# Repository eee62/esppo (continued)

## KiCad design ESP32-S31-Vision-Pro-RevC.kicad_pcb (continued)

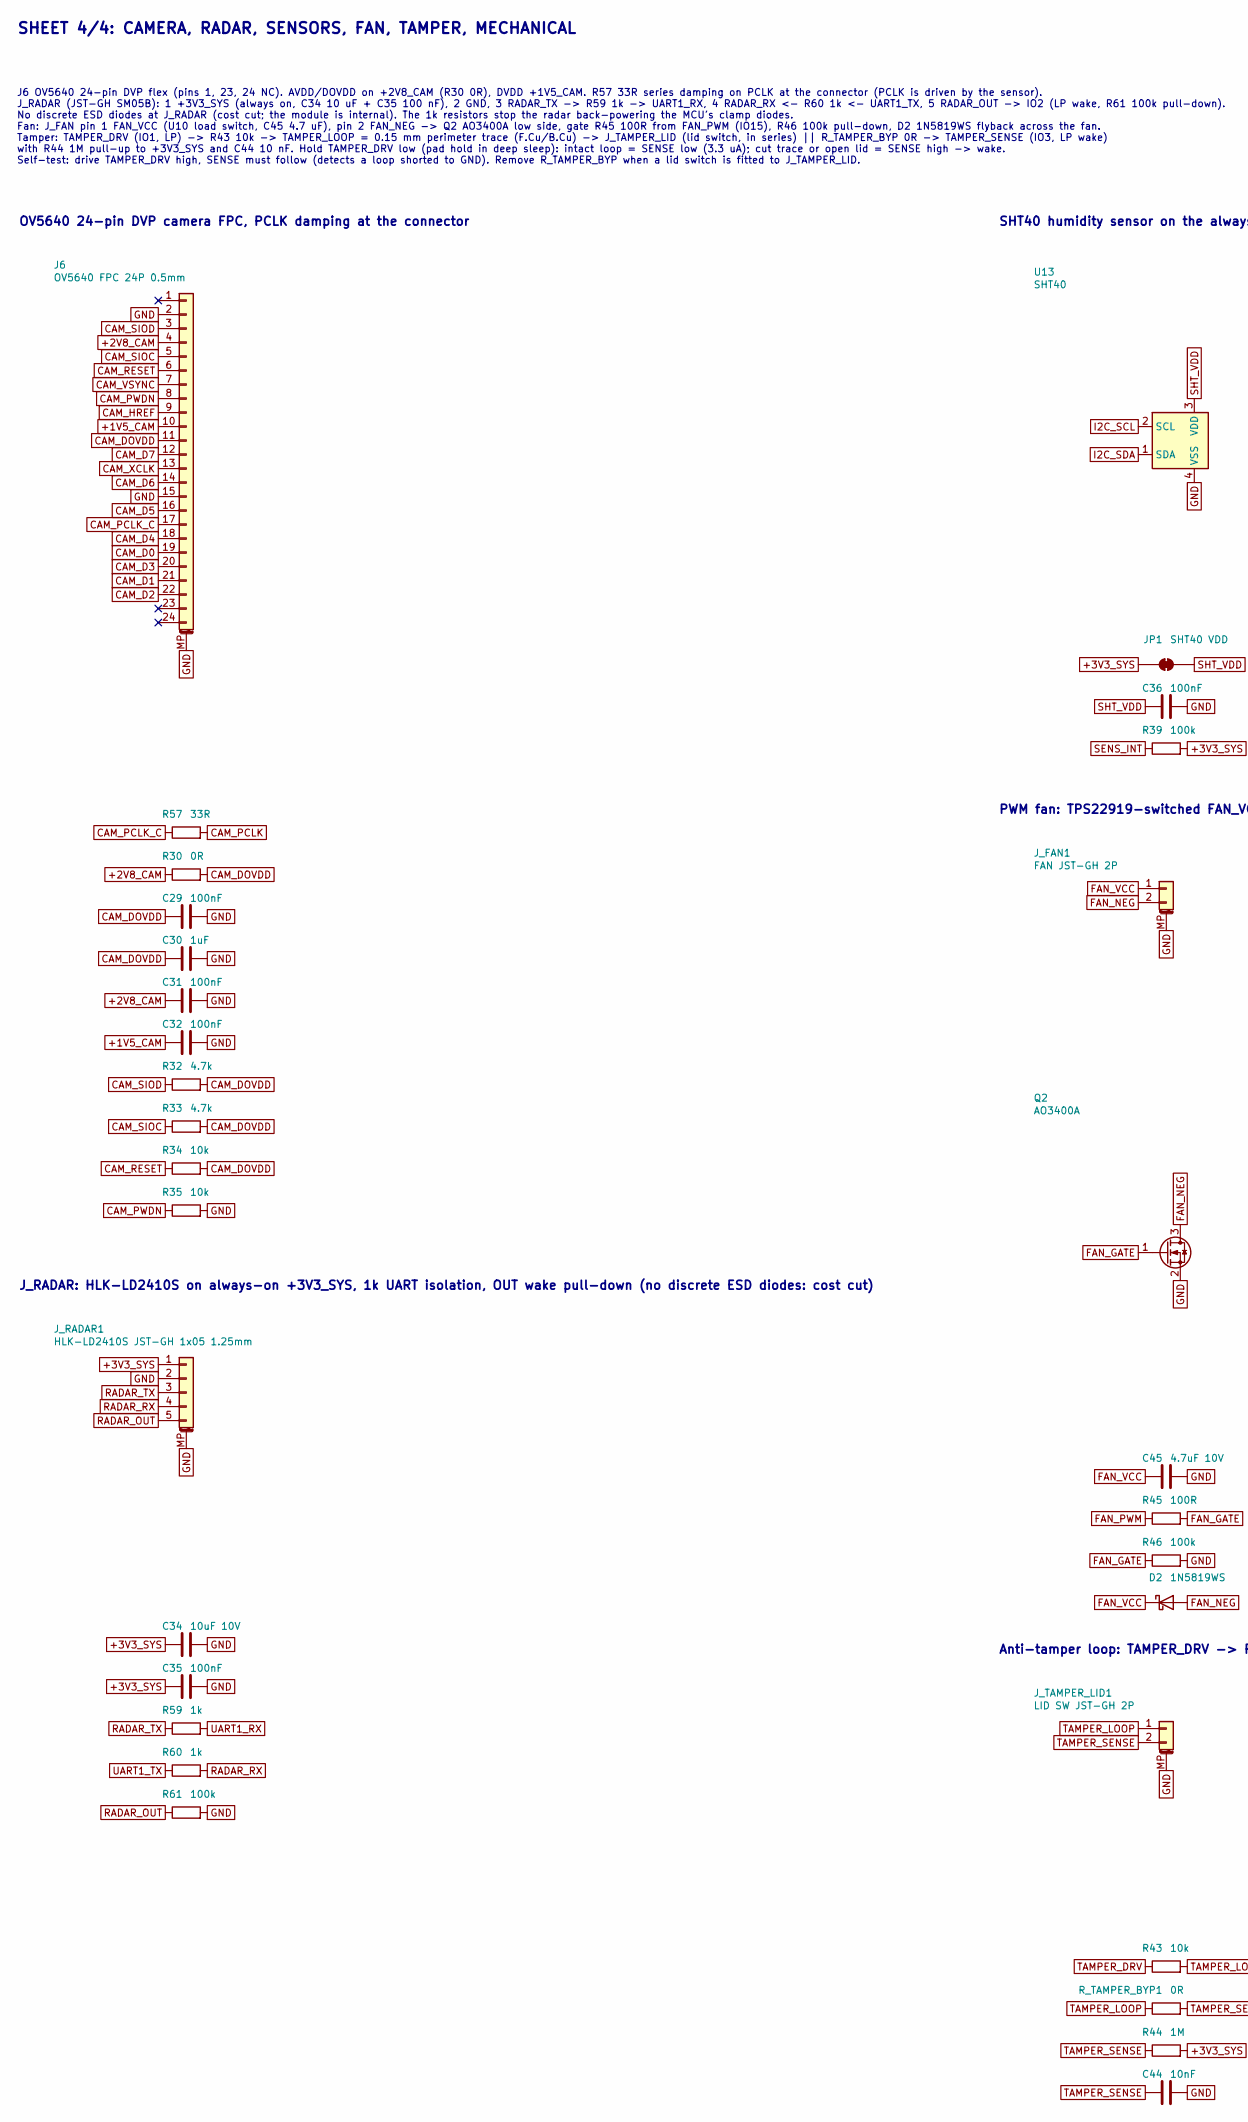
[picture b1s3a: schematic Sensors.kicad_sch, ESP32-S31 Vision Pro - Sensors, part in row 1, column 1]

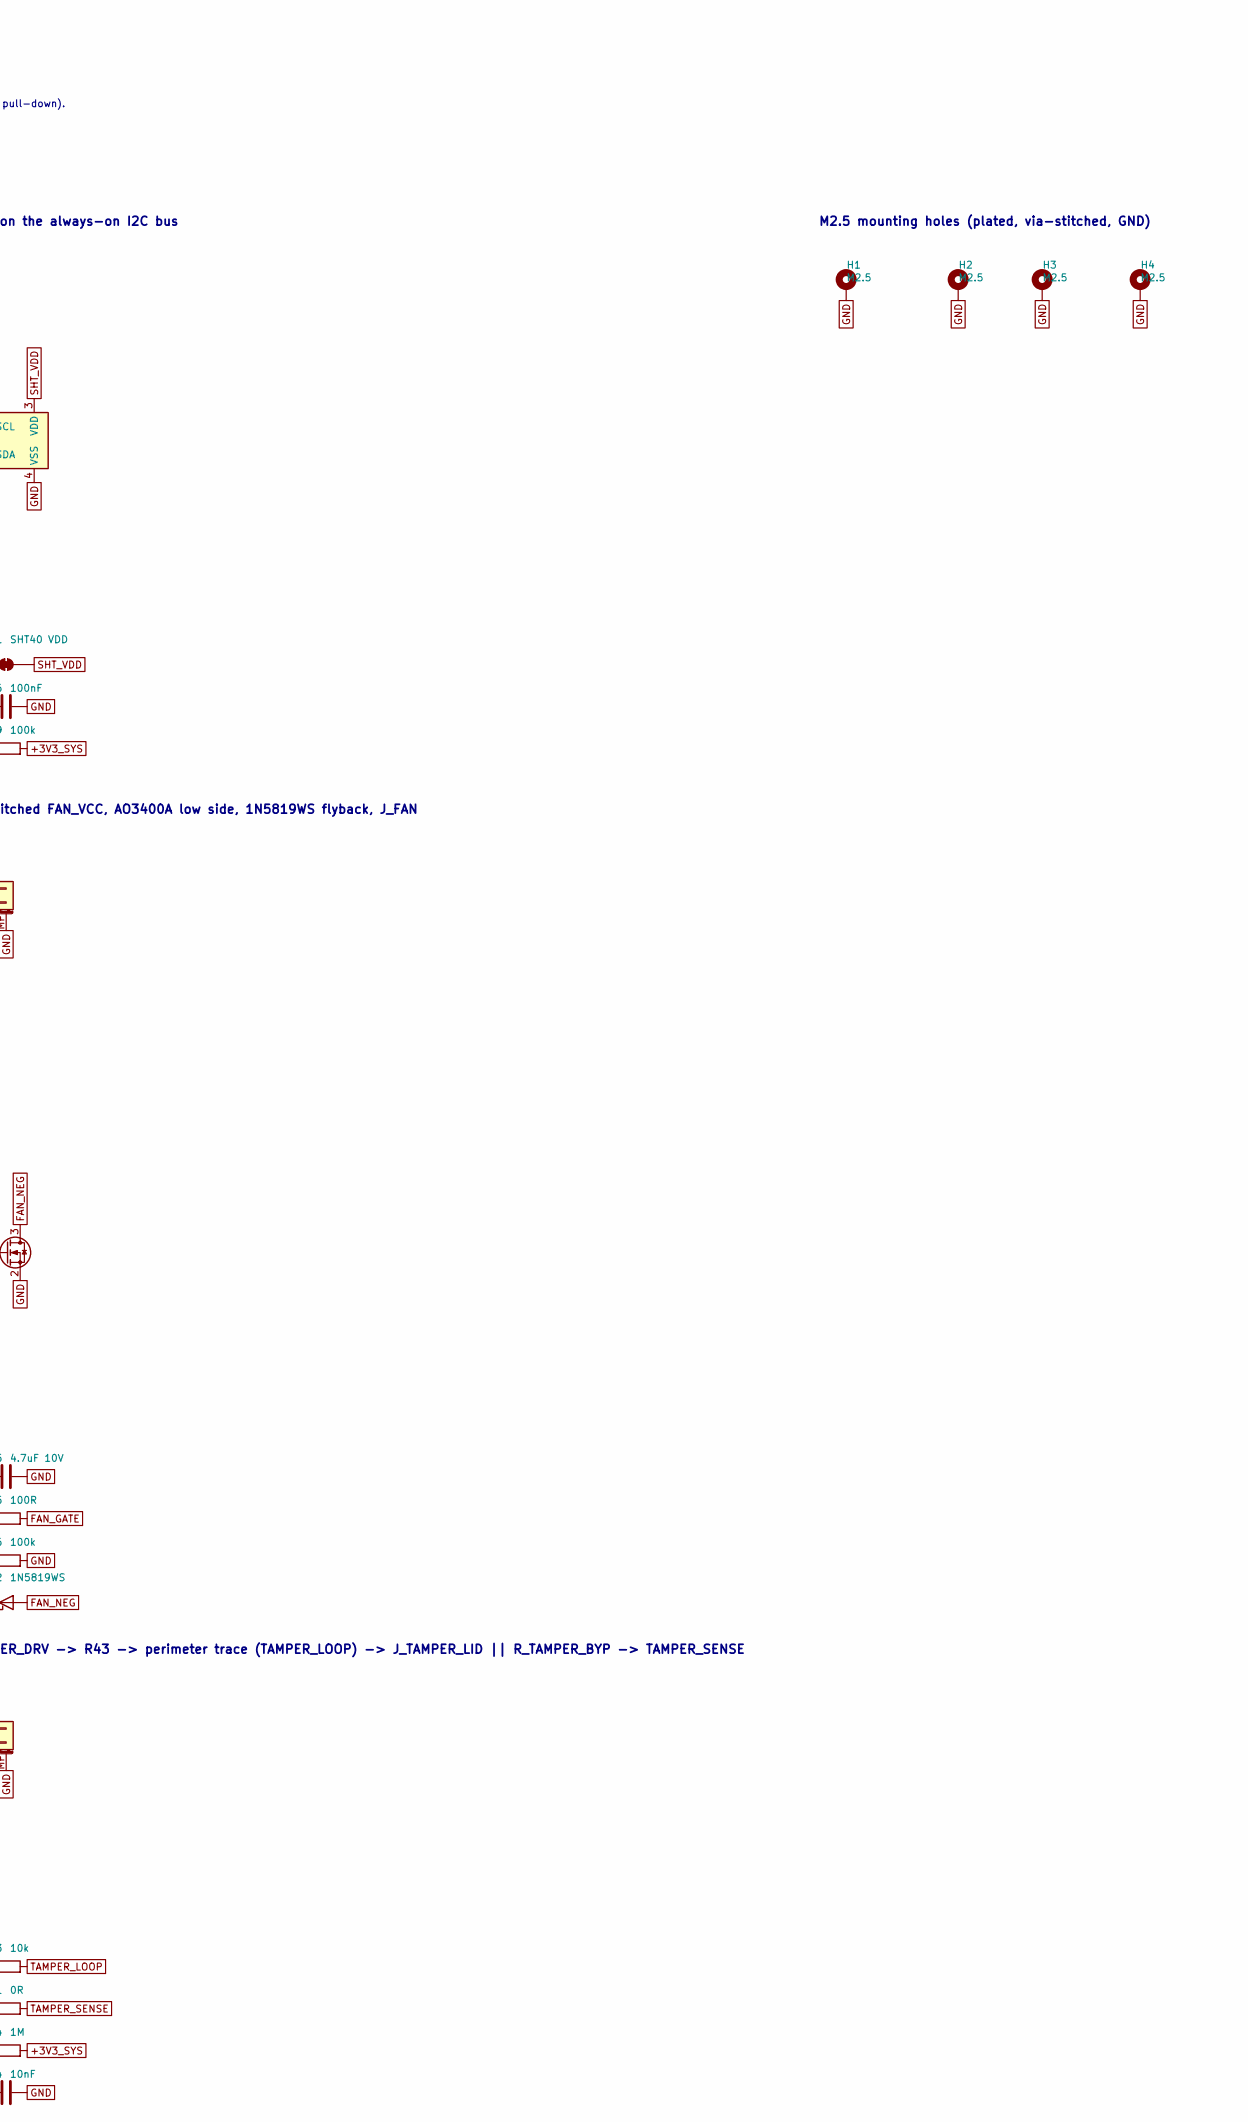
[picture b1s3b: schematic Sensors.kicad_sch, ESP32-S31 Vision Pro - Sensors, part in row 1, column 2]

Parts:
C29, C31, C32, C35, C36: 100nF; C_0402_1005Metric; MPN CL05B104KO5NNNC; LCSC C1525
C30: 1uF; C_0402_1005Metric; MPN CL05A105KA5NQNC; LCSC C52923
C34: 10uF 10V; C_0603_1608Metric; MPN CL10A106KP8NNNC; LCSC C19702
C44: 10nF; C_0402_1005Metric; MPN CL05B103KB5NNNC; LCSC C15195
C45: 4.7uF 10V; C_0603_1608Metric; MPN CL10A475KO8NNNC; LCSC C19666
D2: 1N5819WS; D_SOD-323; MPN 1N5819WS; LCSC C191023
H1, H2, H3, H4: M2.5; MountingHole_2.7mm_M2.5_Pad_Via
J6: OV5640 FPC 24P 0.5mm; Hirose_FH12-24S-0.5SH_1x24-1MP_P0.50mm_Horizontal; MPN FH12-24S-0.5SH(55); LCSC C202112
JP1: SHT40 VDD; SolderJumper-2_P1.3mm_Bridged_RoundedPad1.0x1.5mm
J_FAN1: FAN JST-GH 2P; JST_GH_SM02B-GHS-TB_1x02-1MP_P1.25mm_Horizontal; MPN A1257WR-S-2P; LCSC C225125
J_RADAR1: HLK-LD2410S JST-GH 1x05 1.25mm; JST_GH_SM05B-GHS-TB_1x05-1MP_P1.25mm_Horizontal; MPN SM05B-GHS-TB(LF)(SN); LCSC C189896
J_TAMPER_LID1: LID SW JST-GH 2P; JST_GH_SM02B-GHS-TB_1x02-1MP_P1.25mm_Horizontal; MPN A1257WR-S-2P; LCSC C225125
Q2: AO3400A; SOT-23; MPN AO3400A; LCSC C20917
R30: 0R; R_0402_1005Metric; MPN 0402WGF0000TCE; LCSC C17168
R32, R33: 4.7k; R_0402_1005Metric; MPN 0402WGF4701TCE; LCSC C25900
R34, R35, R43: 10k; R_0402_1005Metric; MPN 0402WGF1002TCE; LCSC C25744
R39, R46, R61: 100k; R_0402_1005Metric; MPN 0402WGF1003TCE; LCSC C25741
R44: 1M; R_0402_1005Metric; MPN 0402WGF1004TCE; LCSC C26083
R45: 100R; R_0402_1005Metric; MPN 0402WGF1000TCE; LCSC C25076
R57: 33R; R_0402_1005Metric; MPN 0402WGF330JTCE; LCSC C25105
R59, R60: 1k; R_0402_1005Metric; MPN 0402WGF1001TCE; LCSC C11702
R_TAMPER_BYP1: 0R; R_0603_1608Metric; MPN 0603WAF0000T5E; LCSC C21189
U13: SHT40; Sensirion_DFN-4_1.5x1.5mm_P0.8mm_SHT4x_NoCentralPad; MPN SHT40-AD1F-R2; LCSC C7461846

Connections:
+1V5_CAM: C32.1, J6.10; also elsewhere on the board
+2V8_CAM: C31.1, J6.4, R30.1; also elsewhere on the board
+3V3_SYS: C34.1, C35.1, JP1.1 (A), J_RADAR1.1, R39.2, R44.2; also elsewhere on the board
CAM_D0: J6.19; also elsewhere on the board
CAM_D1: J6.21; also elsewhere on the board
CAM_D2: J6.22; also elsewhere on the board
CAM_D3: J6.20; also elsewhere on the board
CAM_D4: J6.18; also elsewhere on the board
CAM_D5: J6.16; also elsewhere on the board
CAM_D6: J6.14; also elsewhere on the board
CAM_D7: J6.12; also elsewhere on the board
CAM_DOVDD: C29.1, C30.1, J6.11, R30.2, R32.2, R33.2, R34.2
CAM_HREF: J6.9; also elsewhere on the board
CAM_PCLK: R57.2; also elsewhere on the board
CAM_PCLK_C: J6.17, R57.1
CAM_PWDN: J6.8, R35.1; also elsewhere on the board
CAM_RESET: J6.6, R34.1; also elsewhere on the board
CAM_SIOC: J6.5, R33.1; also elsewhere on the board
CAM_SIOD: J6.3, R32.1; also elsewhere on the board
CAM_VSYNC: J6.7; also elsewhere on the board
CAM_XCLK: J6.13; also elsewhere on the board
FAN_GATE: Q2.1 (G), R45.2, R46.1
FAN_NEG: D2.2 (A), J_FAN1.2, Q2.3 (D)
FAN_PWM: R45.1; also elsewhere on the board
FAN_VCC: C45.1, D2.1 (K), J_FAN1.1; also elsewhere on the board
GND: C29.2, C30.2, C31.2, C32.2, C34.2, C35.2, C36.2, C44.2, C45.2, H1.1, H2.1, H3.1, H4.1, J6.2, J6.15, J6.MP (MountPin), J_FAN1.MP (MountPin), J_RADAR1.2, J_RADAR1.MP (MountPin), J_TAMPER_LID1.MP (MountPin), Q2.2 (S), R35.2, R46.2, R61.2, U13.4 (VSS); also elsewhere on the board
I2C_SCL: U13.2 (SCL); also elsewhere on the board
I2C_SDA: U13.1 (SDA); also elsewhere on the board
RADAR_OUT: J_RADAR1.5, R61.1; also elsewhere on the board
RADAR_RX: J_RADAR1.4, R60.2
RADAR_TX: J_RADAR1.3, R59.1
SENS_INT: R39.1; also elsewhere on the board
SHT_VDD: C36.1, JP1.2 (B), U13.3 (VDD)
TAMPER_DRV: R43.1; also elsewhere on the board
TAMPER_LOOP: J_TAMPER_LID1.1, R43.2, R_TAMPER_BYP1.1
TAMPER_SENSE: C44.1, J_TAMPER_LID1.2, R44.1, R_TAMPER_BYP1.2; also elsewhere on the board
UART1_RX: R59.2; also elsewhere on the board
UART1_TX: R60.1; also elsewhere on the board

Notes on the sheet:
SHEET 4/4: CAMERA, RADAR, SENSORS, FAN, TAMPER, MECHANICAL
J6 OV5640 24-pin DVP flex (pins 1, 23, 24 NC). AVDD/DOVDD on +2V8_CAM (R30 0R), DVDD +1V5_CAM. R57 33R series damping on PCLK at the connector (PCLK is driven by the sensor). J_RADAR (JST-GH SM05B): 1 +3V3_SYS (always on, C34 10 uF + C35 100 nF), 2 GND, 3 RADAR_TX -> R59 1k -> UART1_RX, 4 RADAR_RX 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
OV5640 24-pin DVP camera FPC, PCLK damping at the connector
J_RADAR: HLK-LD2410S on always-on +3V3_SYS, 1k UART isolation, OUT wake pull-down (no discrete ESD diodes: cost cut)
SHT40 humidity sensor on the always-on I2C bus
PWM fan: TPS22919-switched FAN_VCC, AO3400A low side, 1N5819WS flyback, J_FAN
Anti-tamper loop: TAMPER_DRV -> R43 -> perimeter trace (TAMPER_LOOP) -> J_TAMPER_LID || R_TAMPER_BYP -> TAMPER_SENSE
M2.5 mounting holes (plated, via-stitched, GND)

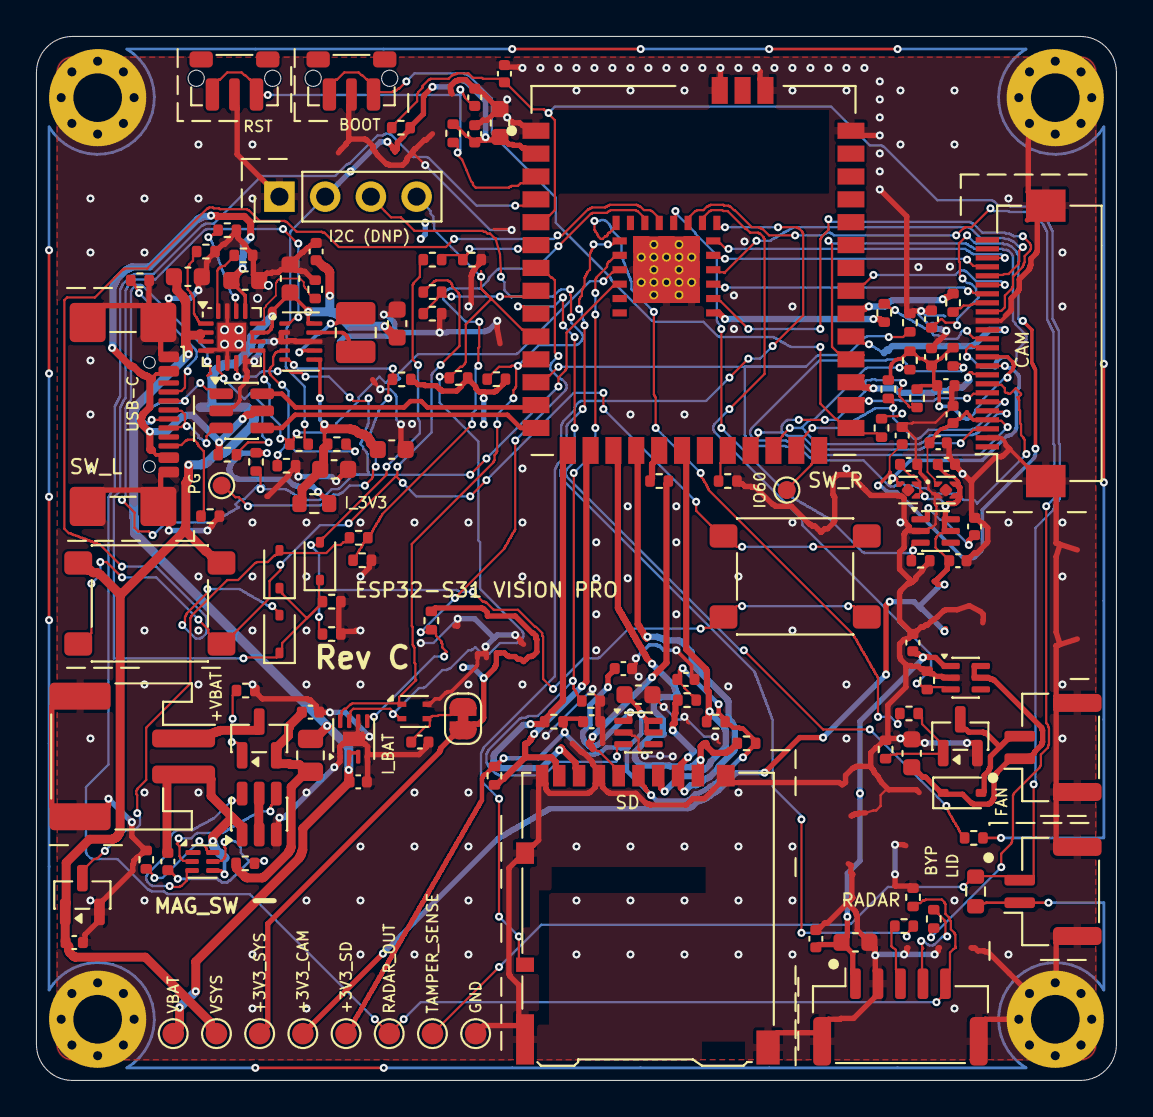
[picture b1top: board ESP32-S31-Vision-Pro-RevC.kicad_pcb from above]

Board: 4 copper layers, 60.0 x 58.0 mm, 137 parts (0 on the bottom side), 94 nets.

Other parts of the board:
C18: 22uF 6.3V; C_0603_1608Metric
C19: 100nF; C_0402_1005Metric
C20: 1uF; C_0402_1005Metric
J3: I2C 1x04 2.54mm header (DNP); PinHeader_1x04_P2.54mm_Vertical
R12, R13, R14: 10k; R_0402_1005Metric
R19, R20: 4.7k; R_0402_1005Metric
R22: 33R; R_0402_1005Metric
SW_BOOT1: BOOT (IO61); SW_Push_1P1T-MP_NO_Horizontal_Alps_SKRTLAE010
SW_RST1: RESET (EN); SW_Push_1P1T-MP_NO_Horizontal_Alps_SKRTLAE010
TP2: IO60; TestPoint_Pad_D1.0mm
U8: ESP32-S31-WROOM-1U

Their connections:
+3V3_SYS: C18.1, C19.1, J3.2, R12.2, R13.2, R19.2, R20.2, U8.2; also elsewhere on the board
CAM_D0: U8.33; also elsewhere on the board
CAM_D1: U8.60; also elsewhere on the board
CAM_D2: U8.61; also elsewhere on the board
CAM_D3: U8.59; also elsewhere on the board
CAM_D4: U8.58; also elsewhere on the board
CAM_D5: U8.57; also elsewhere on the board
CAM_D6: U8.31; also elsewhere on the board
CAM_D7: U8.30; also elsewhere on the board
CAM_HREF: U8.29; also elsewhere on the board
CAM_PCLK: U8.32; also elsewhere on the board
CAM_PWDN: U8.12; also elsewhere on the board
CAM_RESET: U8.25; also elsewhere on the board
CAM_SIOC: U8.24; also elsewhere on the board
CAM_SIOD: U8.23; also elsewhere on the board
CAM_VSYNC: U8.28; also elsewhere on the board
CAM_XCLK: R22.2; also elsewhere on the board
CAM_XCLK_R: R22.1, U8.56
CHG_PGOOD: U8.53; also elsewhere on the board
CHG_STAT: U8.52; also elsewhere on the board
EN_CAM: U8.45; also elsewhere on the board
EN_FAN: U8.43; also elsewhere on the board
EN_SD: U8.51; also elsewhere on the board
ESP_BOOT: R13.1, SW_BOOT1.1, U8.27
ESP_EN: C20.1, R12.1, SW_RST1.1, U8.3
ESP_IO60: TP2.1, U8.26
FAN_PWM: U8.49; also elsewhere on the board
GND: C18.2, C19.2, C20.2, J3.1, R14.2, SW_BOOT1.2, SW_RST1.2, U8.1, U8.40, U8.41, U8.62, U8.64; also elsewhere on the board
HOLD: U8.46; also elsewhere on the board
I2C_SCL: J3.4, R20.1, U8.10; also elsewhere on the board
I2C_SDA: J3.3, R19.1, U8.11; also elsewhere on the board
JTAG_SEL: R14.1, U8.22
RADAR_OUT: U8.4; also elsewhere on the board
SD_CD: U8.42; also elsewhere on the board
SD_CLK_R: U8.19; also elsewhere on the board
SD_CMD: U8.20; also elsewhere on the board
SD_D0: U8.15; also elsewhere on the board
SD_D1: U8.16; also elsewhere on the board
SD_D2: U8.17; also elsewhere on the board
SD_D3: U8.18; also elsewhere on the board
SENSE_L: U8.8; also elsewhere on the board
SENSE_R: U8.6; also elsewhere on the board
SENS_INT: U8.7; also elsewhere on the board
TAMPER_DRV: U8.9; also elsewhere on the board
TAMPER_SENSE: U8.5; also elsewhere on the board
TMR_SENSE: U8.47; also elsewhere on the board
UART1_RX: U8.50; also elsewhere on the board
UART1_TX: U8.44; also elsewhere on the board
USB_DN: U8.13; also elsewhere on the board
USB_DP: U8.14; also elsewhere on the board

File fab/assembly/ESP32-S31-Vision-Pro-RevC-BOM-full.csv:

"Refs","Value","Footprint","Qty","MPN","LCSC","DNP"
"C1","2.2uF 16V","Capacitor_SMD:C_0603_1608Metric","1","CL10A225KO8NNNC","C23630",""
"C2,C45","4.7uF 10V","Capacitor_SMD:C_0603_1608Metric","2","CL10A475KO8NNNC","C19666",""
"C3,C4,C24,C34","10uF 10V","Capacitor_SMD:C_0603_1608Metric","4","CL10A106KP8NNNC","C19702",""
"C5,C19,C25,C29,C31,C32,C35,C36,C46,C47,C48,C49","100nF","Capacitor_SMD:C_0402_1005Metric","12","CL05B104KO5NNNC","C1525",""
"C6,C7,C18","22uF 6.3V","Capacitor_SMD:C_0603_1608Metric","3","CL10A226MQ8NRNC","C59461",""
"C10,C11,C12,C13,C14,C15,C16,C17,C20,C30,C52","1uF","Capacitor_SMD:C_0402_1005Metric","11","CL05A105KA5NQNC","C52923",""
"C44","10nF","Capacitor_SMD:C_0402_1005Metric","1","CL05B103KB5NNNC","C15195",""
"D2","1N5819WS","Diode_SMD:D_SOD-323","1","1N5819WS","C191023",""
"D_HOLD1,D_TMR1,D_WAKE1","BAT54WS","Diode_SMD:D_SOD-323","3","BAT54WS","C7502694",""
"H1,H2,H3,H4","M2.5","MountingHole:MountingHole_2.7mm_M2.5_Pad_Via","4","","",""
"J1","LiPo 1S <=3000mAh (JST-PH)","Connector_JST:JST_PH_S2B-PH-SM4-TB_1x02-1MP_P2.00mm_Horizontal","1","S2B-PH-SM4-TB(LF)(SN)","C295747",""
"J3","I2C 1x04 2.54mm header (DNP)","Connector_PinHeader_2.54mm:PinHeader_1x04_P2.54mm_Vertical","1","","","DNP"
"J5","USB-C","Connector_USB:USB_C_Receptacle_GCT_USB4110","1","USB4110-GF-A","C5143397",""
"J6","OV5640 FPC 24P 0.5mm","Connector_FFC-FPC:Hirose_FH12-24S-0.5SH_1x24-1MP_P0.50mm_Horizontal","1","FH12-24S-0.5SH(55)","C202112",""
"J9","microSD push-push DM3AT-SF-PEJM5","Connector_Card:microSD_HC_Hirose_DM3AT-SF-PEJM5","1","DM3AT-SF-PEJM5","C114218",""
"JP1","SHT40 VDD","Jumper:SolderJumper-2_P1.3mm_Bridged_RoundedPad1.0x1.5mm","1","","",""
"J_FAN1","FAN JST-GH 2P","Connector_JST:JST_GH_SM02B-GHS-TB_1x02-1MP_P1.25mm_Horizontal","1","A1257WR-S-2P","C225125",""
"J_RADAR1","HLK-LD2410S JST-GH 1x05 1.25mm","Connector_JST:JST_GH_SM05B-GHS-TB_1x05-1MP_P1.25mm_Horizontal","1","SM05B-GHS-TB(LF)(SN)","C189896",""
"J_TAMPER_LID1","LID SW JST-GH 2P","Connector_JST:JST_GH_SM02B-GHS-TB_1x02-1MP_P1.25mm_Horizontal","1","A1257WR-S-2P","C225125",""
"L1","0.47uH 4A","Inductor_SMD:L_1008_2520Metric","1","DFE252012F-R47M=P2","C703140",""
"Q1","AO3401A","Package_TO_SOT_SMD:SOT-23","1","AO3401A","C15127",""
"Q2","AO3400A","Package_TO_SOT_SMD:SOT-23","1","AO3400A","C20917",""
"Q3","FS8205A","Package_TO_SOT_SMD:SOT-23-6","1","FS8205A","C908265",""
"R1,R4,R5,R8,R10,R11,R39,R46,R52,R61,R_EN_PD1,R_SENSE_L_BOT1,R_SENSE_R_BOT1","100k","Resistor_SMD:R_0402_1005Metric","13","0402WGF1003TCE","C25741",""
"R2","1.13k 1%","Resistor_SMD:R_0402_1005Metric","1","0402WGF1131TCE","C67014",""
"R3","887R 0.1%","Resistor_SMD:R_0402_1005Metric","1","RT0402BRD07887RL","C852938",""
"R6","56k 1%","Resistor_SMD:R_0402_1005Metric","1","0402WGF5602TCE","C25796",""
"R7","10k 1%","Resistor_SMD:R_0402_1005Metric","1","0402WGF1002TCE","C25744",""
"R12,R13,R14,R34,R35,R43,R50","10k","Resistor_SMD:R_0402_1005Metric","7","0402WGF1002TCE","C25744",""
"R19,R20,R32,R33","4.7k","Resistor_SMD:R_0402_1005Metric","4","0402WGF4701TCE","C25900",""
"R22,R56,R57","33R","Resistor_SMD:R_0402_1005Metric","3","0402WGF330JTCE","C25105",""
"R23,R24,R25,R26,R27,R_SENSE_L_TOP1,R_SENSE_R_TOP1","47k","Resistor_SMD:R_0402_1005Metric","7","0402WGF4702TCE","C25792",""
"R28,R29","5.1k 1%","Resistor_SMD:R_0402_1005Metric","2","0402WGF5101TCE","C25905",""
"R30","0R","Resistor_SMD:R_0402_1005Metric","1","0402WGF0000TCE","C17168",""
"R44,R_TMR_BOT1,R_WAKE_PD1","1M","Resistor_SMD:R_0402_1005Metric","3","0402WGF1004TCE","C26083",""
"R45","100R","Resistor_SMD:R_0402_1005Metric","1","0402WGF1000TCE","C25076",""
"R47","330R","Resistor_SMD:R_0402_1005Metric","1","0402WGF3300TCE","C25104",""
"R48","2.2k","Resistor_SMD:R_0402_1005Metric","1","0402WGF2201TCE","C25879",""
"R49","68k 1%","Resistor_SMD:R_0402_1005Metric","1","0402WGF6802TCE","C36871",""
"R59,R60","1k","Resistor_SMD:R_0402_1005Metric","2","0402WGF1001TCE","C11702",""
"R_MEAS_3V3,R_TAMPER_BYP1","0R","Resistor_SMD:R_0603_1608Metric","2","0603WAF0000T5E","C21189",""
"R_MEAS_BAT1","0R","Resistor_SMD:R_0805_2012Metric","1","0805W8F0000T5E","C17477",""
"R_TMR_TOP1","470k","Resistor_SMD:R_0402_1005Metric","1","0402WGF4703TCE","C25790",""
"SW_BOOT1","BOOT (IO61)","Button_Switch_SMD:SW_Push_1P1T-MP_NO_Horizontal_Alps_SKRTLAE010","1","SKRTLAE010","C110293",""
"SW_L1","SW_L (chord)","Button_Switch_SMD:SW_SPST_PTS645Sx43SMTR92","1","PTS645SK43SMTR92LFS","C221871",""
"SW_R1","SW_R (chord)","Button_Switch_SMD:SW_SPST_PTS645Sx43SMTR92","1","PTS645SK43SMTR92LFS","C221871",""
"SW_RST1","RESET (EN)","Button_Switch_SMD:SW_Push_1P1T-MP_NO_Horizontal_Alps_SKRTLAE010","1","SKRTLAE010","C110293",""
"TH1","10k NTC B3380","Resistor_SMD:R_0402_1005Metric","1","NCP15XH103F03RC","C77131",""
"TP1","PG","TestPoint:TestPoint_Pad_D1.0mm","1","","",""
"TP2","IO60","TestPoint:TestPoint_Pad_D1.0mm","1","","",""
"TP3","VBAT","S31_Vision:TestPoint_Pad_D1.2mm","1","","",""
"TP4","VSYS","S31_Vision:TestPoint_Pad_D1.2mm","1","","",""
"TP5","+3V3_SYS","S31_Vision:TestPoint_Pad_D1.2mm","1","","",""
"TP6","+3V3_CAM","S31_Vision:TestPoint_Pad_D1.2mm","1","","",""
"TP7","+3V3_SD","S31_Vision:TestPoint_Pad_D1.2mm","1","","",""
"TP8","RADAR_OUT","S31_Vision:TestPoint_Pad_D1.2mm","1","","",""
"TP9","TAMPER_SENSE","S31_Vision:TestPoint_Pad_D1.2mm","1","","",""
"TP10","GND","S31_Vision:TestPoint_Pad_D1.2mm","1","","",""
"U1","BQ24075RGTR","Package_DFN_QFN:VQFN-16-1EP_3x3mm_P0.5mm_EP1.6x1.6mm","1","BQ24075RGTR","C15464",""
"U2","TPS63802","S31_Vision:Texas_DLA0010A_VSON-HR-10_2x3mm_P0.5mm","1","TPS63802DLAT","C1849531",""
"U3","TMR3102SO","Package_TO_SOT_SMD:SOT-23","1","TMR3102SO","C7421000",""
"U4,U5,U10","TPS22919DCKR","Package_TO_SOT_SMD:SOT-363_SC-70-6","3","TPS22919DCKR","C2149796",""
"U6","TPS7A2028 (2.8V)","Package_SON:Texas_X2SON-4_1x1mm_P0.65mm","1","TPS7A2028PDQNR-A-TP","C55191366",""
"U7","TPS7A2015 (1.5V)","Package_SON:Texas_X2SON-4_1x1mm_P0.65mm","1","TPS7A2015PDQNR","C2862700",""
"U8","ESP32-S31-WROOM-1U","S31_Vision:ESP32-S31-WROOM-1U","1","ESP32-S31-WROOM-1U","",""
"U11","USBLC6-2SC6","Package_TO_SOT_SMD:SOT-23-6","1","USBLC6-2SC6","C7519",""
"U13","SHT40","Sensor_Humidity:Sensirion_DFN-4_1.5x1.5mm_P0.8mm_SHT4x_NoCentralPad","1","SHT40-AD1F-R2","C7461846",""
"U18","BQ29700DSET","Package_SON:WSON-6_1.5x1.5mm_P0.5mm","1","BQ29700DSET","C2876282",""
"U19","MAX17048G+T10","Package_DFN_QFN:TDFN-8-1EP_2x2mm_P0.5mm_EP0.8x1.2mm","1","MAX17048G+T10","C2682616",""
